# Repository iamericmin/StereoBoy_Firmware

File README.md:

# StereoBoy Firmware

Open-source firmware & hardware files for StereoBoy, the portable & modular stereo system!

The firmware project is organized as a Pico-SDK project that you can import directly into VSCode with Raspberry Pi's official Raspberry Pi Pico extension. You might need to git clone the [no-OS-FatFS-SD-SDIO-SPI-RPi-Pico repository](https://hackaday.io/project/205771-stereoboy).

The KiCad_files contains the full KiCad project should you want to produce your own PCBs. Make sure to order them in 1mm thickness, or else they won't fit into a GameBoy Pocket shell properly!!!

## What is this?

### FULL DISCLAIMER: I use AI-generated code for parts of this project! AI was used mainly for debugging and quick prototyping.

StereoBoy is a portable audio player I designed to be fit inside an original GameBoy Pocket shell. Read more about it here: [Hackaday Project Page](https://hackaday.io/project/205771-stereoboy)

**My main focus on the software side is providing a no-BS listening experience. For me, this implies a few things:**

 - Instant boot-up time
 - Intuitive UI that should ideally be easy enough to use without a manual
 - Simple, snappy UI that provides quick navigation between tracks, albums, artists, etc.
 - Easy to load music, with no software to manage file transfer
 - Plus the usual features such as an album art, equalizer, fast forward/rewind, etc.

So far, I've achieved sub-1s boot time that instantly provides a simple, iPod-like menu for albums, artists, and tracks as soon as you turn the device on, with a snappy interface that allows navigating through thousands of tracks with zero noticeable lag.

Music is loaded simply by dragging and dropping audio files on a micro-SD card, although a python script needs to be run to update the system cache with new track metadata. The script takes about 1.5 minutes to parse through a library of a little over 2000 songs. Thanks to the pre-generated metadata cache files, StereoBoy can instantly load fully sorted menus and crisp album artwork pretty much instantaneously.

Currently I have a very rudimentary equalizer going as well as buttery smooth fast forward/rewind. MP3s are the only supported file format, but I plan on adding FLAC support too.

**However, I also wanted to add some of my own personality to give the firmware some charm. Examples include:**

 - warp effect when pausing/resuming to simulate an analog tape reel. It's my favorite part of the entire project and never ever gets annoying.
 - Oscilloscope visualizer that displays super-high FPS waveforms of left and right channel audio
 - Audio plays at slightly lower speed and pitch on low battery to simulate a dying walkman (work in progress!)

## Let's get technical
### Here's a block diagram of the firmware architecture:

The firmware runs in a producer-consumer architecture, with Core 0 acting as the producer and Core 1 as the consumer. Core 0 mainly handles low-level peripherals and filesystem IO, such as opening/reading files and parsing track metadata. Core 1 mainly handles graphics and UI, reading data generated by Core 0 and rendering the appropriate visualizer/interface on the display and LEDs.

Both cores run their own superloop with very few interrupt-based routines. The firmware originally started out as a quick prototyping exercise for some core components, but eventually snowballed into what it is right now, and frankly I think it works alright for the task at hand. The current firmware architecture made it pretty easy to add features and modify existing components.

### Now here's a block diagram of the hardware architecture:

While the star of the show is an RP2350B microcontroller, it's actually a VS1063 audio codec that does the heavy lifting of all things related to audio. The RP2350's two cores handle user interface logic, graphics, and filesystem operations, while the codec crunches through audio data and provides the RP2350 with analog audio data, along with other useful tidbits of info such as playback timestamp or sampling frequency.

I2S output from the VS1063 is sent to a TLV320DAC3100, which is an integrated I2S DAC and headphone/speaker amp. It also controls the final output volume. The display is a 240x240 1.54" TFT LCD, and there is twin-bar VU meter for some extra flair. Currently it's only used as a visualizer but I plan on implementing more features into it, such as a battery level indicator. There is an 8KB FRAM chip to store last played track data plus some settings, and an 8-bit shift register takes care of all eight buttons to output to a single GPIO pin on the RP2350.

The power supply is a "double decker" structure where two PCBs are stacked on top of each other, with the top half containing the priority mux and 5V boost, while the bottom half contains the 1.8V and 3.3V buck regulators.

## The Future
### What do I have planned for the future?

 - 5-band graphic equalizer
 - Queue/play next
 - High-FPS FFT visualizer
 - Playlists
 - FLAC support
 - Last played song and timestamp available on boot-up
 - Settings to choose interface options and colors
 - Extras, like a timer/stopwatch/calendar
 - Games, like music quiz
 - More intuitive UI, some parts are a little clunky to use

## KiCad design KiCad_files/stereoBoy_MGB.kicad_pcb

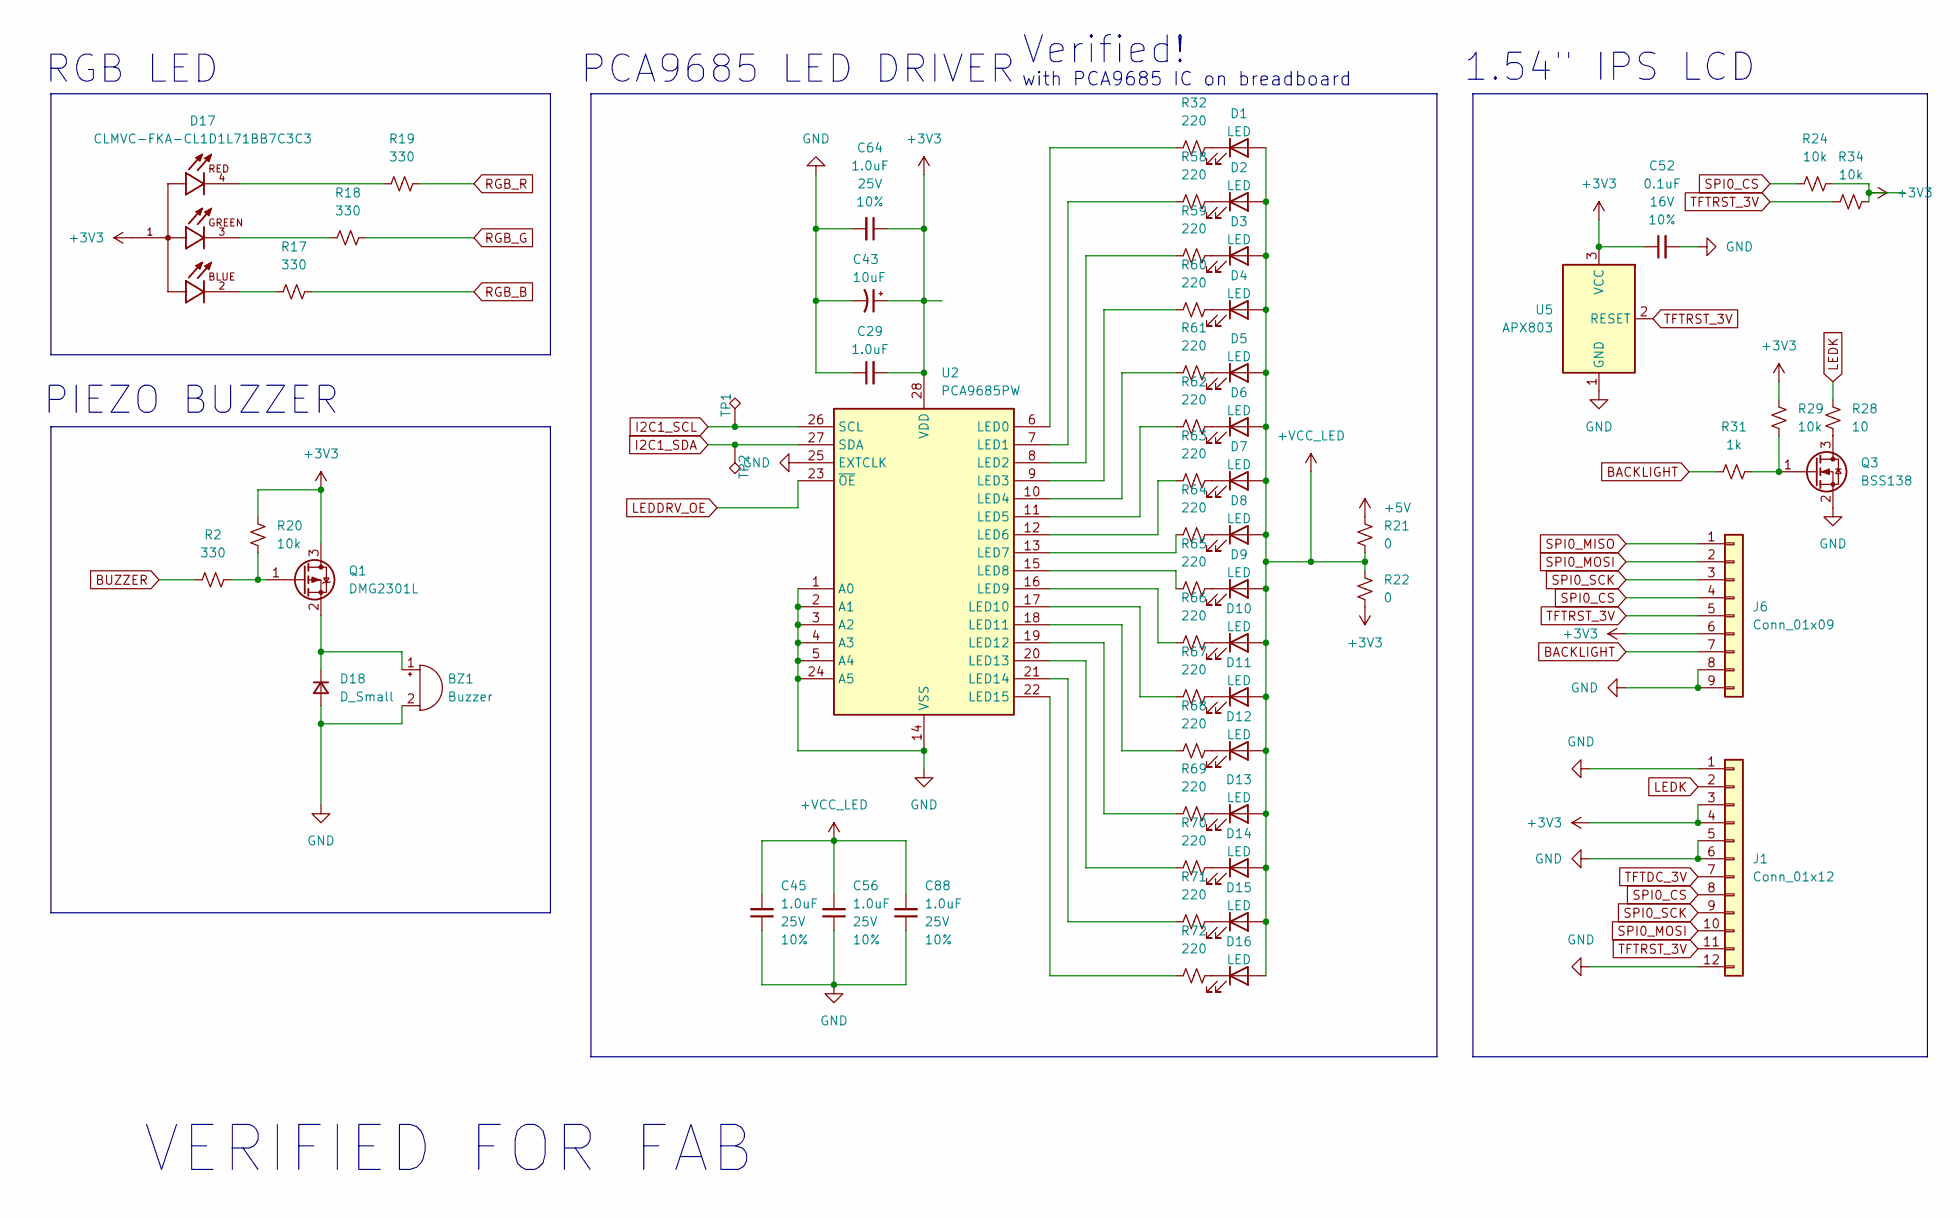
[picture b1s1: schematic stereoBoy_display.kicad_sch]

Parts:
BZ1: Buzzer; Buzzer_CUI_CPT-9019S-SMT
C29, C64: 1.0uF; C_0805_2012Metric; Voltage 25V; Tolerance 10%
C43: 10uF; CP_Elec_6.3x4.5; Voltage 6.3V; Tolerance 20%
C45, C56, C88: 1.0uF; C_1206_3216Metric; Voltage 25V; Tolerance 10%
C52: 0.1uF; C_0402_1005Metric; Voltage 16V; Tolerance 10%
D1, D2, D3, D4, D5, D6, D7, D8, D9, D10, D11, D12, D13, D14, D15, D16: LED; LED_D3.0mm
D17: CLMVC-FKA-CL1D1L71BB7C3C3; CREE_LED_2mm_x_2mm_Common_Anode; PARTREV 14
D18: D_Small; D_0603_1608Metric
J1: Conn_01x12; 1.54_IPS_FPC_Solder
J6: Conn_01x09; 1x09_P2.54mm
Q1: DMG2301L; SOT-23
Q3: BSS138; SOT-23
R2: 330; R_0603_1608Metric
R17, R18, R19: 330; R_0402_1005Metric
R20, R24, R29, R34: 10k; R_0603_1608Metric
R21, R22: 0; R_0603_1608Metric
R28: 10; R_0603_1608Metric
R31: 1k; R_0603_1608Metric
R32, R58, R59, R60, R61, R62, R63, R64, R65, R66, R67, R68, R69, R70, R71, R72: 220; R_0402_1005Metric
TP1, TP2: TestPoint_Alt; TestPoint_Pad_D1.0mm
U2: PCA9685PW; TSSOP-28_4.4x9.7mm_P0.65mm
U5: APX803; SOT-23

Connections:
+3V3: C29.2, C43.1, C52.1, C64.1, D17.1, J1.3, J1.4, J6.6, Q1.3 (D), R20.2, R22.1, R24.1, R29.2, R34.1, U2.28 (VDD), U5.3 (VCC); also elsewhere on the board
+5V: R21.2; also elsewhere on the board
+VCC_LED: C45.2, C56.2, C88.2, D1.2 (A), D2.2 (A), D3.2 (A), D4.2 (A), D5.2 (A), D6.2 (A), D7.2 (A), D8.2 (A), D9.2 (A), D10.2 (A), D11.2 (A), D12.2 (A), D13.2 (A), D14.2 (A), D15.2 (A), D16.2 (A), R21.1, R22.2
BACKLIGHT: J6.7, R31.2; also elsewhere on the board
BUZZER: R2.1; also elsewhere on the board
GND: BZ1.2 (-), C29.1, C43.2, C45.1, C52.2, C56.1, C64.2, C88.1, D18.2 (A), J1.1, J1.5, J1.6, J1.12, J6.8, J6.9, Q3.2 (S), U2.1 (A0), U2.2 (A1), U2.3 (A2), U2.4 (A3), U2.5 (A4), U2.14 (VSS), U2.24 (A5), U2.25 (EXTCLK), U5.1 (GND); also elsewhere on the board
I2C1_SCL: TP1.1, U2.26 (SCL); also elsewhere on the board
I2C1_SDA: TP2.1, U2.27 (SDA); also elsewhere on the board
LEDDRV_OE: U2.23 (~OE); also elsewhere on the board
LEDK: J1.2, R28.2
unnamed: BZ1.1 (+), D18.1 (K), Q1.2 (S)
unnamed: D1.1 (K), R32.2
unnamed: D2.1 (K), R58.2
unnamed: D3.1 (K), R59.2
unnamed: D4.1 (K), R60.2
unnamed: D5.1 (K), R61.2
unnamed: D6.1 (K), R62.2
unnamed: D7.1 (K), R63.2
unnamed: D8.1 (K), R64.2
unnamed: D9.1 (K), R65.2
unnamed: D10.1 (K), R66.2
unnamed: D11.1 (K), R67.2
unnamed: D12.1 (K), R68.2
unnamed: D13.1 (K), R69.2
unnamed: D14.1 (K), R70.2
unnamed: D15.1 (K), R71.2
unnamed: D16.1 (K), R72.2
unnamed: D17.2, R17.1
unnamed: D17.3, R18.1
unnamed: D17.4, R19.1
unnamed: Q1.1 (G), R2.2, R20.1
unnamed: Q3.3 (D), R28.1
unnamed: Q3.1 (G), R29.1, R31.1
unnamed: R32.1, U2.6 (LED0)
unnamed: R58.1, U2.7 (LED1)
unnamed: R59.1, U2.8 (LED2)
unnamed: R60.1, U2.9 (LED3)
unnamed: R61.1, U2.10 (LED4)
unnamed: R62.1, U2.11 (LED5)
unnamed: R63.1, U2.12 (LED6)
unnamed: R64.1, U2.13 (LED7)
unnamed: R65.1, U2.15 (LED8)
unnamed: R66.1, U2.16 (LED9)
unnamed: R67.1, U2.17 (LED10)
unnamed: R68.1, U2.18 (LED11)
unnamed: R69.1, U2.19 (LED12)
unnamed: R70.1, U2.20 (LED13)
unnamed: R71.1, U2.21 (LED14)
unnamed: R72.1, U2.22 (LED15)
RGB_B: R17.2; also elsewhere on the board
RGB_G: R18.2; also elsewhere on the board
RGB_R: R19.2; also elsewhere on the board
SPI0_CS: J1.8, J6.4, R24.2; also elsewhere on the board
SPI0_MISO: J6.1; also elsewhere on the board
SPI0_MOSI: J1.10, J6.2; also elsewhere on the board
SPI0_SCK: J1.9, J6.3; also elsewhere on the board
TFTDC_3V: J1.7; also elsewhere on the board
TFTRST_3V: J1.11, J6.5, R34.2, U5.2 (RESET); also elsewhere on the board

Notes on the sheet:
1.54" IPS LCD
with PCA9685 IC on breadboard
PIEZO BUZZER
RGB LED
Verified!
VERIFIED FOR FAB
PCA9685 LED DRIVER

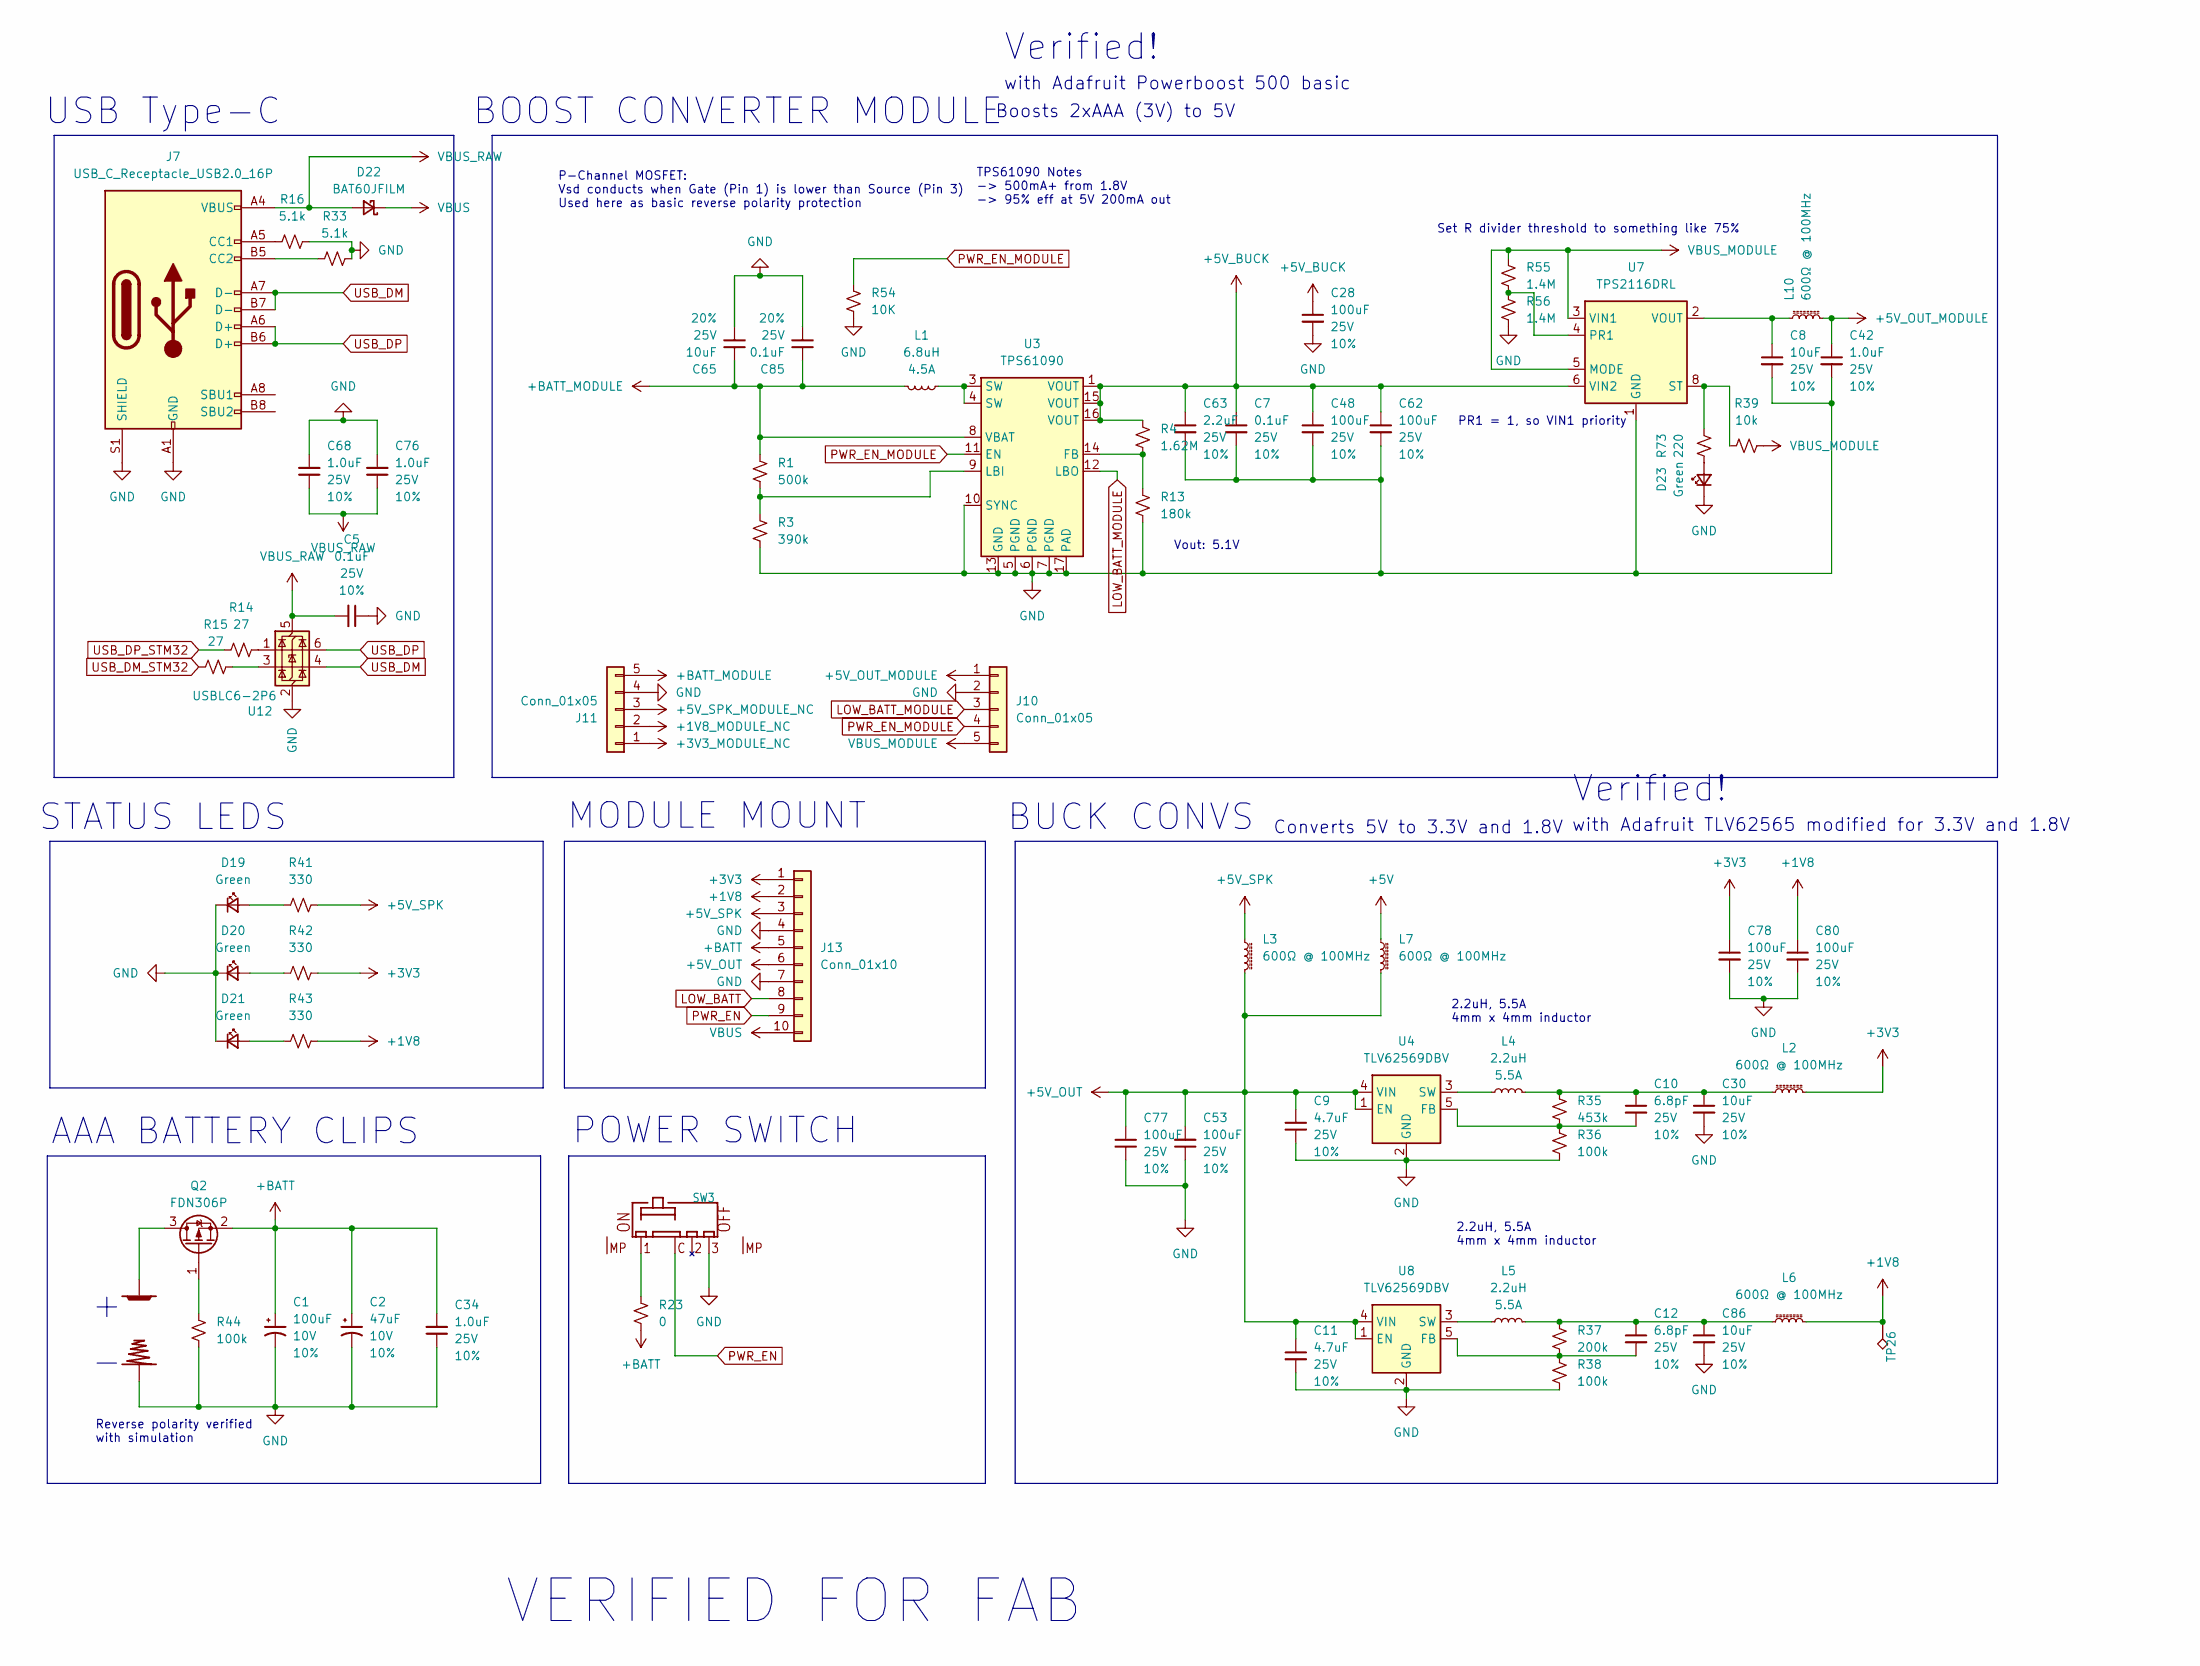
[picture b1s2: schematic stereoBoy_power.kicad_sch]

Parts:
+0: MGB+BATTERY4
-0: MGB-BATTERY4
C1: 100uF; CP_EIA-7343-15_Kemet-W_HandSolder; Voltage 10V; Tolerance 10%
C2: 47uF; CP_EIA-7343-15_Kemet-W_HandSolder; Voltage 10V; Tolerance 10%
C5: 0.1uF; C_0402_1005Metric; Voltage 25V; Tolerance 10%
C7: 0.1uF; C_0603_1608Metric; Voltage 25V; Tolerance 10%
C8: 10uF; C_1206_3216Metric; Voltage 25V; Tolerance 10%
C9, C11: 4.7uF; C_0805_2012Metric; Voltage 25V; Tolerance 10%
C10, C12: 6.8pF; C_0805_2012Metric; Voltage 25V; Tolerance 10%
C28: 100uF; C_0603_1608Metric; Voltage 25V; Tolerance 10%
C30, C86: 10uF; C_0805_2012Metric; Voltage 25V; Tolerance 10%
C34, C42: 1.0uF; C_1206_3216Metric; Voltage 25V; Tolerance 10%
C48, C53, C62, C77, C78, C80: 100uF; C_1206_3216Metric; Voltage 25V; Tolerance 10%
C63: 2.2uF; C_0603_1608Metric; Voltage 25V; Tolerance 10%
C65: 10uF; C_0603_1608Metric; Voltage 25V; Tolerance 20%
C68, C76: 1.0uF; C_0805_2012Metric; Voltage 25V; Tolerance 10%
C85: 0.1uF; C_0603_1608Metric; Voltage 25V; Tolerance 20%
D19, D20, D21: Green; LED_0603_1608Metric_Green
D22: BAT60JFILM; SOD-323
D23: Green; LED_1206_3216Metric_Green
J7: USB_C_Receptacle_USB2.0_16P; USB_C_Receptacle_GCT_USB4105-xx-A_16P_TopMnt_Horizontal
J10, J11: Conn_01x05; 1x05_P2.54mm
J13: Conn_01x10; StereoBoy_PSU
L1: 6.8uH; Inductor_7.3x6.6mm
L2, L6: 600Ω @ 100MHz; C_0603_1608Metric
L3, L7: 600Ω @ 100MHz; L_0603_1608Metric
L4, L5: 2.2uH; L_APV_ANR3012
L10: 600Ω @ 100MHz; L_0805_2012Metric
Q2: FDN306P; SOT-23
R1: 500k; R_0603_1608Metric
R3: 390k; R_0603_1608Metric
R4: 1.62M; C_0402_1005Metric
R13: 180k; C_0402_1005Metric
R14, R15: 27; C_0402_1005Metric
R16, R33: 5.1k; R_0603_1608Metric
R23: 0; R_0603_1608Metric
R35: 453k; R_0603_1608Metric
R36, R38: 100k; R_0603_1608Metric
R37: 200k; R_0603_1608Metric
R39: 10k; R_0603_1608Metric
R41, R42, R43: 330; R_0402_1005Metric
R44: 100k; R_0805_2012Metric
R54: 10K; R_0402_1005Metric
R55, R56: 1.4M; R_0603_1608Metric
R73: 220; R_0603_1608Metric
SW3: MGB-SW1; GBP_Power_Switch
TP26: TestPoint_Alt; TestPoint_Pad_D1.0mm
U3: TPS61090; Texas_RSA_VQFN-16-1EP_4x4mm_P0.65mm_EP2.7x2.7mm_ThermalVias
U4, U8: TLV62569DBV; SOT-23-5
U7: TPS2116DRL; SOT-583-8
U12: USBLC6-2P6; SOT-666

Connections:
+1V8: C80.1, J13.2, L6.2, R43.2, TP26.1; also elsewhere on the board
+1V8_MODULE_NC: J11.2
+3V3: C78.1, J13.1, L2.2, R42.2; also elsewhere on the board
+3V3_MODULE_NC: J11.1
+5V: L7.1; also elsewhere on the board
+5V_BUCK: C7.1, C28.1, C48.1, C62.1, C63.1, R4.1, U3.1 (VOUT), U3.15 (VOUT), U3.16 (VOUT), U7.6 (VIN2)
+5V_OUT: C9.1, C11.1, C53.2, C77.1, J13.6, L3.2, L7.2, U4.1 (EN), U4.4 (VIN), U8.1 (EN), U8.4 (VIN)
+5V_OUT_MODULE: C42.1, J10.1, L10.2
+5V_SPK: J13.3, L3.1, R41.2; also elsewhere on the board
+5V_SPK_MODULE_NC: J11.3
+BATT: C1.1, C2.1, C34.2, J13.5, Q2.2 (S), R23.1
+BATT_MODULE: C65.1, C85.1, J11.5, L1.2, R1.1, U3.8 (VBAT)
GND: -0.P$1, -0.P$3, -0.P$4, C1.2, C2.2, C5.1, C7.2, C8.2, C9.2, C11.2, C28.2, C30.2, C34.1, C42.2, C48.2, C53.1, C62.2, C63.2, C65.2, C68.2, C76.2, C77.2, C78.2, C80.2, C85.2, C86.2, D19.1 (K), D20.1 (K), D21.1 (K), D23.1 (K), J7.A1 (GND), J7.A12 (GND), J7.B1 (GND), J7.B12 (GND), J7.S1 (SHIELD), J10.2, J11.4, J13.4, J13.7, R3.2, R13.2, R16.2, R33.2, R36.2, R38.2, R44.1, R54.2, R56.2, SW3.P$3 (3), U3.5 (PGND), U3.6 (PGND), U3.7 (PGND), U3.10 (SYNC), U3.13 (GND), U3.17 (PAD), U4.2 (GND), U7.1 (GND), U8.2 (GND), U12.2 (GND); also elsewhere on the board
LOW_BATT: J13.8; also elsewhere on the board
LOW_BATT_MODULE: J10.3, U3.12 (LBO)
unnamed: C8.1, L10.1, U7.2 (VOUT), U7.7 (VOUT)
unnamed: C10.1, C30.1, L2.1, L4.2, R35.1
unnamed: C12.1, C86.1, L5.2, L6.1, R37.1
unnamed: D19.2 (A), R41.1
unnamed: D20.2 (A), R42.1
unnamed: D21.2 (A), R43.1
unnamed: D23.2 (A), R73.1
unnamed: J7.A5 (CC1), R16.1
unnamed: J7.B5 (CC2), R33.1
unnamed: L1.1, U3.3 (SW), U3.4 (SW)
unnamed: +0.P$1, +0.P$2, +0.P$3, Q2.3 (D)
unnamed: Q2.1 (G), R44.2
unnamed: R14.2, U12.1 (I/O1)
unnamed: R15.2, U12.3 (I/O2)
unnamed: R23.2, SW3.P$1 (1)
unnamed: R4.2, R13.1, U3.14 (FB)
unnamed: R1.2, R3.1, U3.9 (LBI)
unnamed: C10.2, R35.2, R36.1, U4.5 (FB)
unnamed: L4.1, U4.3 (SW)
unnamed: R55.2, R56.1, U7.4 (PR1)
unnamed: R39.1, R73.2, U7.8 (ST)
unnamed: C12.2, R37.2, R38.1, U8.5 (FB)
unnamed: L5.1, U8.3 (SW)
PWR_EN: J13.9, SW3.P$C (C)
PWR_EN_MODULE: J10.4, R54.1, U3.11 (EN)
USB_DM: J7.A7 (D-), J7.B7 (D-), U12.4 (I/O2)
USB_DM_STM32: R15.1; also elsewhere on the board
USB_DP: J7.A6 (D+), J7.B6 (D+), U12.6 (I/O1)
USB_DP_STM32: R14.1; also elsewhere on the board
VBUS: D22.1 (K), J13.10
VBUS_MODULE: J10.5, R39.2, R55.1, U7.3 (VIN1), U7.5 (MODE)
VBUS_RAW: C5.2, C68.1, C76.1, D22.2 (A), J7.A4 (VBUS), J7.A9 (VBUS), J7.B4 (VBUS), J7.B9 (VBUS), U12.5 (VBUS)

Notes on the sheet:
with Adafruit Powerboost 500 basic
Vout: 5.1V
AAA BATTERY CLIPS
2.2uH, 5.5A 4mm x 4mm inductor
MODULE MOUNT
BUCK CONVS
STATUS LEDS
with Adafruit TLV62565 modified for 3.3V and 1.8V
Converts 5V to 3.3V and 1.8V
PR1 = 1, so VIN1 priority
POWER SWITCH
Reverse polarity verified with simulation
Boosts 2xAAA (3V) to 5V
Set R divider threshold to something like 75%
P-Channel MOSFET: Vsd conducts when Gate (Pin 1) is lower than Source (Pin 3) Used here as basic reverse polarity protection
USB Type-C
BOOST CONVERTER MODULE
VERIFIED FOR FAB
Verified!
TPS61090 Notes -> 500mA+ from 1.8V -> 95% eff at 5V 200mA out

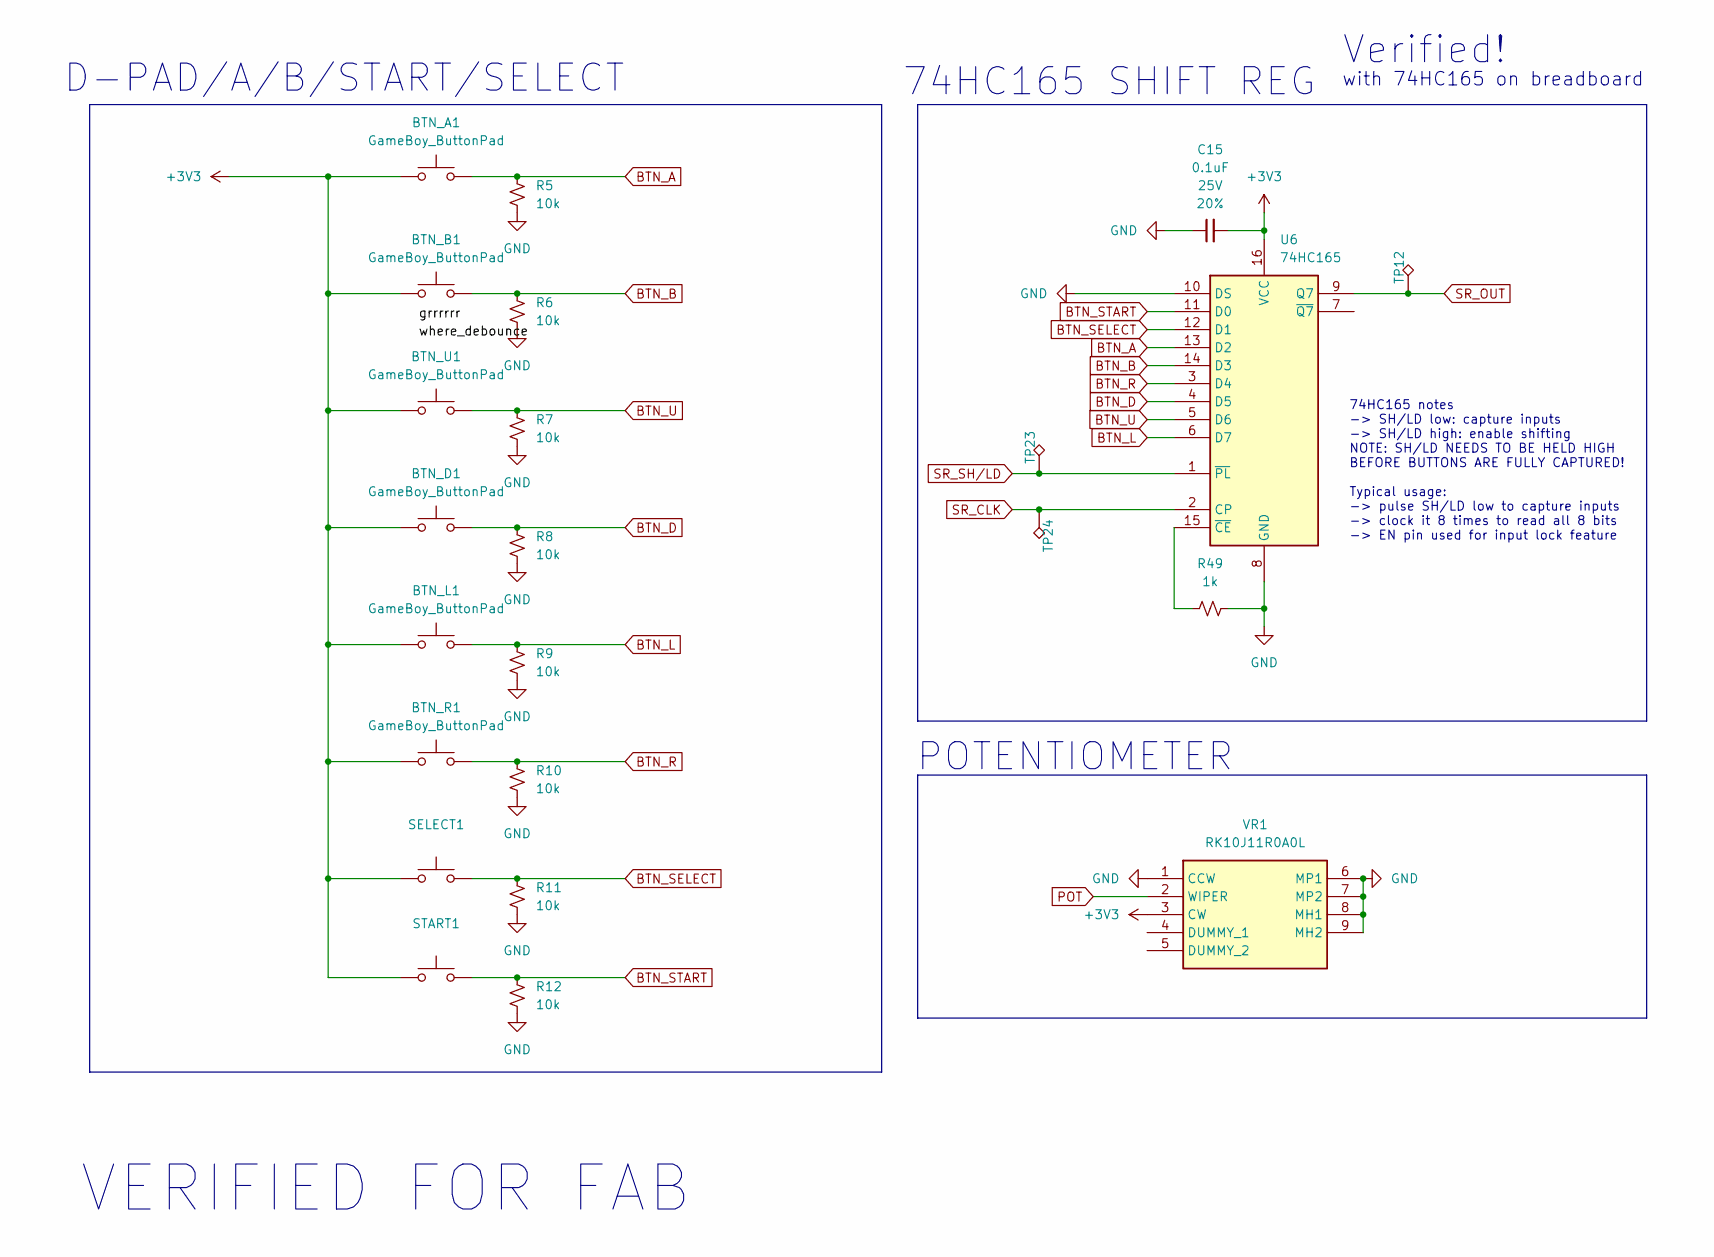
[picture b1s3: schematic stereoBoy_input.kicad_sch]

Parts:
BTN_A1: GameBoy_ButtonPad; GameBoy_A_B_Pad
BTN_B1: GameBoy_ButtonPad; GameBoy_A_B_Pad
BTN_D1: GameBoy_ButtonPad; GameBoy_DPad
BTN_L1: GameBoy_ButtonPad; GameBoy_DPad
BTN_R1: GameBoy_ButtonPad; GameBoy_DPad
BTN_U1: GameBoy_ButtonPad; GameBoy_DPad
C15: 0.1uF; C_0402_1005Metric; Voltage 25V; Tolerance 20%
R5, R6, R7, R8, R9, R10, R11, R12: 10k; R_0603_1608Metric
R49: 1k; R_0402_1005Metric
SELECT1: SMD_6x3.5mm_h2.5mm; GameBoy_Select_Start; Mfg Part# 8-004 SMD Button 8x3.6mm Height=2.5mm
START1: SMD_6x3.5mm_h2.5mm; GameBoy_Select_Start; Mfg Part# 8-004 SMD Button 8x3.6mm Height=2.5mm
TP12, TP23, TP24: TestPoint_Alt; TestPoint_Pad_D1.0mm
U6: 74HC165; TSSOP-16_4.4x5mm_P0.65mm
VR1: RK10J11R0A0L; Manufacturer_Part_Number RK10J11R0A0L; Mouser Part Number 688-RK10J11R0A0L

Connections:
+3V3: BTN_A1.1, BTN_B1.1, BTN_D1.1, BTN_L1.1, BTN_R1.1, BTN_U1.1, C15.2, SELECT1.1, START1.1, U6.16 (VCC), VR1.3 (CW); also elsewhere on the board
BTN_A: BTN_A1.2, R5.2, U6.13 (D2)
BTN_B: BTN_B1.2, R6.2, U6.14 (D3)
BTN_D: BTN_D1.2, R8.2, U6.4 (D5)
BTN_L: BTN_L1.2, R9.2, U6.6 (D7)
BTN_R: BTN_R1.2, R10.2, U6.3 (D4)
BTN_SELECT: R11.2, SELECT1.2, U6.12 (D1)
BTN_START: R12.2, START1.2, U6.11 (D0)
BTN_U: BTN_U1.2, R7.2, U6.5 (D6)
GND: C15.1, R5.1, R6.1, R7.1, R8.1, R9.1, R10.1, R11.1, R12.1, R49.2, U6.8 (GND), U6.10 (DS), VR1.1 (CCW), VR1.6 (MP1), VR1.7 (MP2), VR1.8 (MH1), VR1.9 (MH2); also elsewhere on the board
unnamed: R49.1, U6.15 (~CE)
POT: VR1.2 (WIPER); also elsewhere on the board
SR_CLK: TP24.1, U6.2 (CP); also elsewhere on the board
SR_OUT: TP12.1, U6.9 (Q7); also elsewhere on the board
SR_SH/LD: TP23.1, U6.1 (~PL); also elsewhere on the board

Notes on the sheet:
74HC165 SHIFT REG
Verified!
D-PAD/A/B/START/SELECT
VERIFIED FOR FAB
74HC165 notes -> SH/LD low: capture inputs -> SH/LD high: enable shifting NOTE: SH/LD NEEDS TO BE HELD HIGH BEFORE BUTTONS ARE FULLY CAPTURED! Typical usage: -> pulse SH/LD low to capture inputs -> clock it 8 times to read all 8 bits -> EN pin used for input lock feature
with 74HC165 on breadboard
POTENTIOMETER

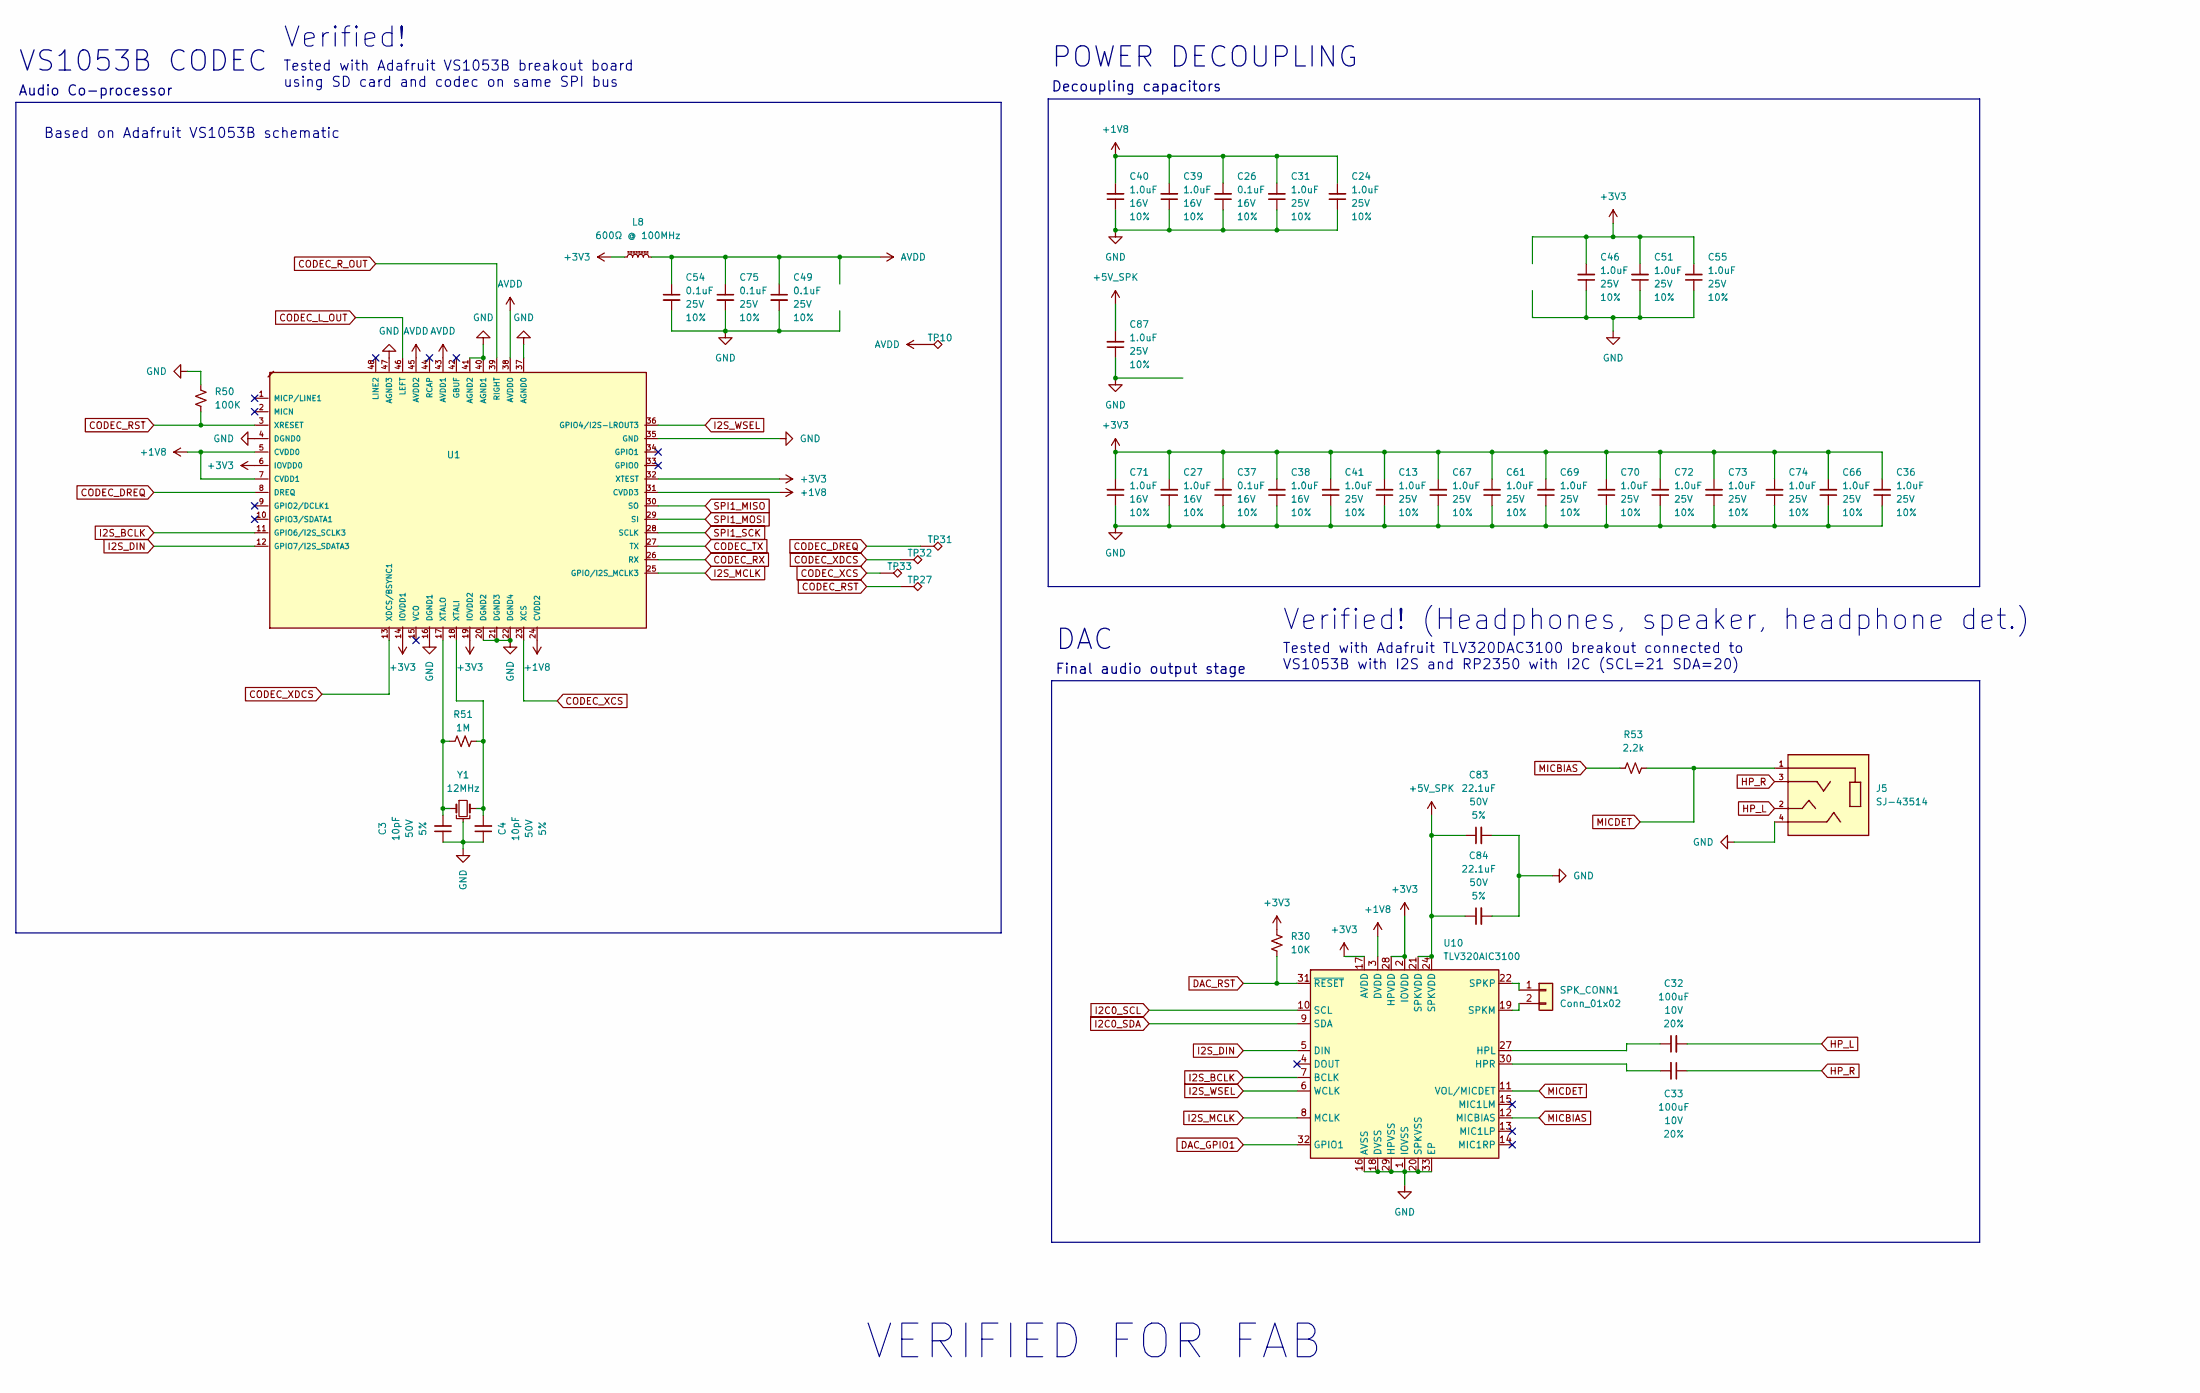
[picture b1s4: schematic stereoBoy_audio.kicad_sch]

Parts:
C3, C4: 10pF; C_0402_1005Metric; Voltage 50V; Tolerance 5%
C13, C24, C31, C36, C41: 1.0uF; C_0402_1005Metric; Voltage 25V; Tolerance 10%
C26, C37: 0.1uF; C_0402_1005Metric; Voltage 16V; Tolerance 10%
C27, C38, C39, C40, C71: 1.0uF; C_0402_1005Metric; Voltage 16V; Tolerance 10%
C32, C33: 100uF; C_1206_3216Metric; Voltage 10V; Tolerance 20%
C46, C51, C55, C66, C67, C70, C72, C73, C74: 1.0uF; C_1206_3216Metric; Voltage 25V; Tolerance 10%
C49, C75: 0.1uF; C_0402_1005Metric; Voltage 25V; Tolerance 10%
C54: 0.1uF; C_0603_1608Metric; Voltage 25V; Tolerance 10%
C61, C69, C87: 1.0uF; C_0805_2012Metric; Voltage 25V; Tolerance 10%
C83, C84: 22.1uF; C_0402_1005Metric; Voltage 50V; Tolerance 5%
J5: SJ-43514; SJ_43514; PART_REV 1.04
L8: 600Ω @ 100MHz; C_0603_1608Metric
R30: 10K; R_0402_1005Metric
R50: 100K; R_0402_1005Metric
R51: 1M; R_0402_1005Metric
R53: 2.2k; R_0402_1005Metric
SPK_CONN1: Conn_01x02; 1x02
TP10, TP27, TP31, TP32, TP33: TestPoint_Alt; TestPoint_Pad_D1.0mm
U1: VS1053B-lqfp48; VS1053b; MPN VS1053B
U10: TLV320AIC3100; VQFN-32-1EP_5x5mm_P0.5mm_EP3.5x3.5mm
Y1: 12MHz; Crystal_SMD_3225-4Pin_3.2x2.5mm

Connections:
+1V8: C24.2, C26.2, C31.2, C39.2, C40.2, U1.5 (CVDD0), U1.7 (CVDD1), U1.24 (CVDD2), U1.31 (CVDD3), U10.3 (DVDD); also elsewhere on the board
+3V3: C13.2, C27.2, C36.2, C37.2, C38.2, C41.2, C46.2, C51.2, C55.2, C61.2, C66.2, C67.2, C69.2, C70.2, C71.2, C72.2, C73.2, C74.2, L8.1, R30.2, U1.6 (IOVDD0), U1.14 (IOVDD1), U1.19 (IOVDD2), U1.32 (XTEST), U10.2 (IOVDD), U10.17 (AVDD), U10.28 (HPVDD); also elsewhere on the board
+5V_SPK: C83.1, C84.1, C87.2, U10.21 (SPKVDD), U10.24 (SPKVDD); also elsewhere on the board
AVDD: C49.1, C54.1, C75.1, L8.2, TP10.1, U1.38 (AVDD0), U1.43 (AVDD1), U1.45 (AVDD2)
CODEC_DREQ: TP31.1, U1.8 (DREQ); also elsewhere on the board
CODEC_L_OUT: U1.46 (LEFT); also elsewhere on the board
CODEC_RST: R50.1, TP27.1, U1.3 (XRESET); also elsewhere on the board
CODEC_RX: U1.26 (RX)
CODEC_R_OUT: U1.39 (RIGHT); also elsewhere on the board
CODEC_TX: U1.27 (TX)
CODEC_XCS: TP33.1, U1.23 (XCS); also elsewhere on the board
CODEC_XDCS: TP32.1, U1.13 (XDCS/BSYNC1); also elsewhere on the board
DAC_GPIO1: U10.32 (GPIO1); also elsewhere on the board
DAC_RST: R30.1, U10.31 (~RESET); also elsewhere on the board
GND: C3.1, C4.1, C13.1, C24.1, C26.1, C27.1, C31.1, C36.1, C37.1, C38.1, C39.1, C40.1, C41.1, C46.1, C49.2, C51.1, C54.2, C55.1, C61.1, C66.1, C67.1, C69.1, C70.1, C71.1, C72.1, C73.1, C74.1, C75.2, C83.2, C84.2, C87.1, J5.4, R50.2, U1.4 (DGND0), U1.16 (DGND1), U1.20 (DGND2), U1.21 (DGND3), U1.22 (DGND4), U1.35 (GND), U1.37 (AGND0), U1.40 (AGND1), U1.41 (AGND2), U1.47 (AGND3), U10.1 (IOVSS), U10.16 (AVSS), U10.18 (DVSS), U10.20 (SPKVSS), U10.25 (SPKVSS), U10.29 (HPVSS), U10.33 (EP), Y1.2, Y1.4; also elsewhere on the board
HP_L: C32.2, J5.2
HP_R: C33.1, J5.3
I2C0_SCL: U10.10 (SCL); also elsewhere on the board
I2C0_SDA: U10.9 (SDA); also elsewhere on the board
I2S_BCLK: U1.11 (GPIO6/I2S_SCLK3), U10.7 (BCLK); also elsewhere on the board
I2S_DIN: U1.12 (GPIO7/I2S_SDATA3), U10.5 (DIN); also elsewhere on the board
I2S_MCLK: U1.25 (GPIO/I2S_MCLK3), U10.8 (MCLK); also elsewhere on the board
I2S_WSEL: U1.36 (GPIO4/I2S-LROUT3), U10.6 (WCLK); also elsewhere on the board
MICBIAS: R53.2, U10.12 (MICBIAS)
MICDET: J5.1, R53.1, U10.11 (VOL/MICDET)
unnamed: SPK_CONN1.1, U10.22 (SPKP), U10.26 (SPKP)
unnamed: SPK_CONN1.2, U10.19 (SPKM), U10.23 (SPKM)
unnamed: C4.2, R51.1, U1.18 (XTALI), Y1.3
unnamed: C3.2, R51.2, U1.17 (XTALO), Y1.1
unnamed: C32.1, U10.27 (HPL)
unnamed: C33.2, U10.30 (HPR)
SPI1_MISO: U1.30 (SO); also elsewhere on the board
SPI1_MOSI: U1.29 (SI); also elsewhere on the board
SPI1_SCK: U1.28 (SCLK); also elsewhere on the board

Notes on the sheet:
DAC
VERIFIED FOR FAB
POWER DECOUPLING
Tested with Adafruit TLV320DAC3100 breakout connected to VS1053B with I2S and RP2350 with I2C (SCL=21 SDA=20)
Verified!
Tested with Adafruit VS1053B breakout board using SD card and codec on same SPI bus
Based on Adafruit VS1053B schematic
Decoupling capacitors
Audio Co-processor
VS1053B CODEC
Final audio output stage
Verified! (Headphones, speaker, headphone det.)
